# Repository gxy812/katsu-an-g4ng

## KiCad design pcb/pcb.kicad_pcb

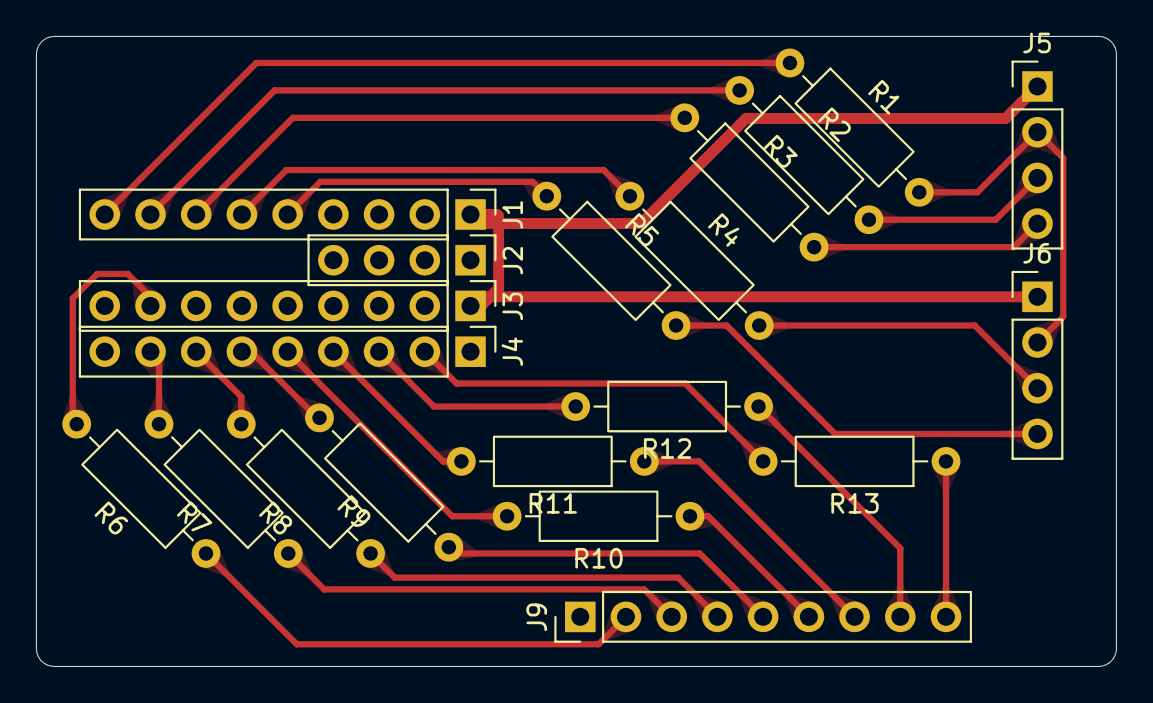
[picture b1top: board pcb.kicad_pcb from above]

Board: 2 copper layers, 60.0 x 35.0 mm, 20 parts (0 on the bottom side), 28 nets.

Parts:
J1, J3, J4, J9: Pin1x9; PinHeader_1x09_P2.54mm_Vertical
J2, J5, J6: Pin1x4; PinHeader_1x04_P2.54mm_Vertical
R1, R2, R3, R4, R5, R6, R7, R8, R9, R10, R11, R12, R13: 330; R_Axial_DIN0207_L6.3mm_D2.5mm_P10.16mm_Horizontal

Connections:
+3V3: J1.1, J3.1, J5.1, J6.1
/B.2: J4.2, R13.2
/B.5: J4.3, R12.2
/B.8: J4.4, R11.2
/B.11: J4.5, R10.2
/B.14: J4.6, R9.2
/B.17: J4.7, R8.2
/B.20: J4.8, R7.2
/B.21: J3.8, R6.2
/B.27: J1.9, R1.1
/B.30: J1.8, R2.1
/B.33: J1.7, R3.1
/B.36: J1.6, R4.1
/B.39: J1.5, R5.1
GND: J2.1, J4.1, J9.1
unnamed: J5.2, J6.2, R1.2
unnamed: J5.3, R2.2
unnamed: J5.4, R3.2
unnamed: J6.3, R4.2
unnamed: J6.4, R5.2
unnamed: J9.2, R6.1
unnamed: J9.3, R7.1
unnamed: J9.4, R8.1
unnamed: J9.5, R9.1
unnamed: J9.6, R10.1
unnamed: J9.7, R11.1
unnamed: J9.8, R12.1
unnamed: J9.9, R13.1

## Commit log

2026-03-15 add deadline
2026-03-15 feat: modules and tests for alu - 13 alu operations
2026-03-15 feat: alchitry top for lab5, hexadecimal support in seven segments
2026-03-16 chore: organise files into folders - not visible from alchitry but nicer in folder
2026-03-16 feat: new instructions: rotate, reverse, and absolute - currently without testbenches
2026-03-17 feat: testbench for rotation operations
2026-03-17 feat: test and debug absolute and reverse modules
2026-03-17 fix: typo where addition is used instead of OR
2026-03-17 feat: add new instructions to alu testbench
2026-03-17 feat: integrate new instructions into automatic tester
2026-03-17 fix: fsm no longer skips first test case, remove unused left_shifter module
2026-03-17 fix: decrease DIV for real world to make it slightly faster
2026-03-17 Uploaded image and game demo
    Image from Nano Banana 2. Game Demo from Claude Sonnet 4.6 and Gemini 3 Fast.
2026-03-18 comments added
2026-03-18 z v m flags added to io led[2] lowest 3 bits
2026-03-18 Added regfile components
    Added two components and edited the json in the .alp file
2026-03-18 added pc_unit.luc and sourcefile definition for it
2026-03-18 added motherboard.luc and source definition
2026-03-19 Changed the file type from .sv to .luc
    Whoops, mb, I didn't see the file type previously. I don't think I need to change the alchitry json right?
2026-03-19 chore: organise alp file for easier importing from the rest of lab 6
2026-03-19 chore: import provided beta cpu modules from lab 6
2026-03-19 BETA CPU V1
    Not fully checked
2026-03-19 feat: finish beta_cpu according to lab and test bench
2026-03-20 feat: lab6 completion except for custom test instructions
2026-03-20 Added Custom Instructions, and Changed MUL and MULC from ILLOP to the correct CU_ROM number
2026-03-20 Beta assembler
2026-03-20 feat: import max7219 code from prof github with some changes - not working for multiple units yet
2026-03-21 chore: formatting
2026-03-21 fix: change to fpga implementation of multiply to remove timing error and since we know the original one works anyway
2026-03-21 feat: change constraints so that matrix pins are driven with less current
2026-03-21 feat: testbench for serial, data now pushed in correct (reverse) order - still have corruption on the display - either some timing issue or logic level issue
2026-03-22 chore: clean up now unnecessary reverses in driver, intensity setup moved back to startup section
2026-03-22 test: identified chain logic as source of issues - difference in behaviour between chain=1 and ignoring chain entirely
2026-03-22 feat: it works - double chain and pad and it somehow works
2026-03-23 format: align comments
2026-03-23 test: new test case that shows different inputs across displays
2026-03-23 wip: display unit and integration with cpu
2026-03-23 disabled mul in control unit, will need to see what to do with multiplier unit in the future
2026-03-23 Changed ROL opcode from 0x00 to 0x10, so that 0x00 is left for special commands
2026-03-23 feat: display unit working independently - not yet tested with beta cpu stores
2026-03-24 feat: beta cpu integrated with display unit - updates a bit too fast for the display to refresh properly but displays mostly as intended
2026-03-24 README
2026-03-26 test: halve stored bits in chain - still functioning
2026-03-26 wip: lab6 checkoff instructions
2026-03-27 feat: lab6 checkoff instructions
2026-03-30 Updated irq handeling for control unit
2026-04-01 fix: machine code referred to wrong registers
2026-04-01 Squashed 'beta-assembler/' content from commit eda501b
    git-subtree-dir: beta-assembler
    git-subtree-split: eda501ba8a20df8a1706f671be6a830aaefebba7
2026-04-01 chore: change beta-assembler to subtree and merge changes back in
2026-04-01 feat: change the size of the simulator board
2026-04-01 feat: simulator that writes 16 rows - maybe should change the orientation of the simulator
2026-04-02 feat: corrected simulator orientation and removed walls
2026-04-02 chore: clean up unecessary data in data segment
2026-04-02 save irq directly into the memory
2026-04-03 fix: counter was off by one
2026-04-03 feat: intialise PCB schematic
2026-04-05 Initial commit for orphan branch
2026-04-09 feat: completion of pcb
2026-04-09 feat: completion of pcb routing
2026-04-09 chore: fillet corners
2026-04-10 chore: reorganise resistors and wire paths
2026-04-10 feat: export to fabrication output
2026-04-10 chore: annotation cleanup
2026-04-10 chore: reexport on advice of fab lab
2026-04-12 feat: add rotate instructions to simulator - doesn't show properly in disassembler but works
2026-04-12 chore: add .venv to ignore
2026-04-12 feat: most of code done - rotation logic, collision checking, rendering of entire map but without sprites
2026-04-13 added datarom and the corresponding connections
2026-04-13 added button checks
2026-04-13 unfudged all files
2026-04-13 not sure if correct but wrote logic for reading data from datarom
2026-04-13 edited motherboard state logic
2026-04-13 revert: bad commit
2026-04-14 wip: start screen & rom fetching
2026-04-14 feat: both displays out
2026-04-14 feat: displays working most of the time - need to replug sometimes to get them to initialize properly- still have non working first row
2026-04-14 merged data rom and memory rom, fixed motherboard logic
2026-04-14 changed label for map data
2026-04-14 added sprite blocks
2026-04-14 wip: both displays working except for lowest row/column
2026-04-14 chore: make tester automatic
2026-04-14 feat: integrate irq
2026-04-14 fix: -1 doesnt actually seem to be hFF
2026-04-14 wrong sprite 1 fixed
2026-04-14 wip: attempt fix irq
2026-04-14 wip: final day cutoff
2026-04-15 wip: final morning - remove unnecessary xp in branch instruction
2026-04-15 wip: final morning - update with led output
2026-04-15 wip: final morning - irq motherboard code is wrong
2026-04-15 wip: final final
2026-04-16 wip: working scroller and sprites
2026-04-16 feat: working map load and scrolling
2026-04-16 wip: more game tweaks to get it to display well and correct left right input
2026-04-16 feat: both displays are stable and neither of them is blinking
2026-04-16 feat: make game faster and dont end for both players on one death
2026-04-16 feat: pretty much done
2026-04-17 feat: change starting player position
